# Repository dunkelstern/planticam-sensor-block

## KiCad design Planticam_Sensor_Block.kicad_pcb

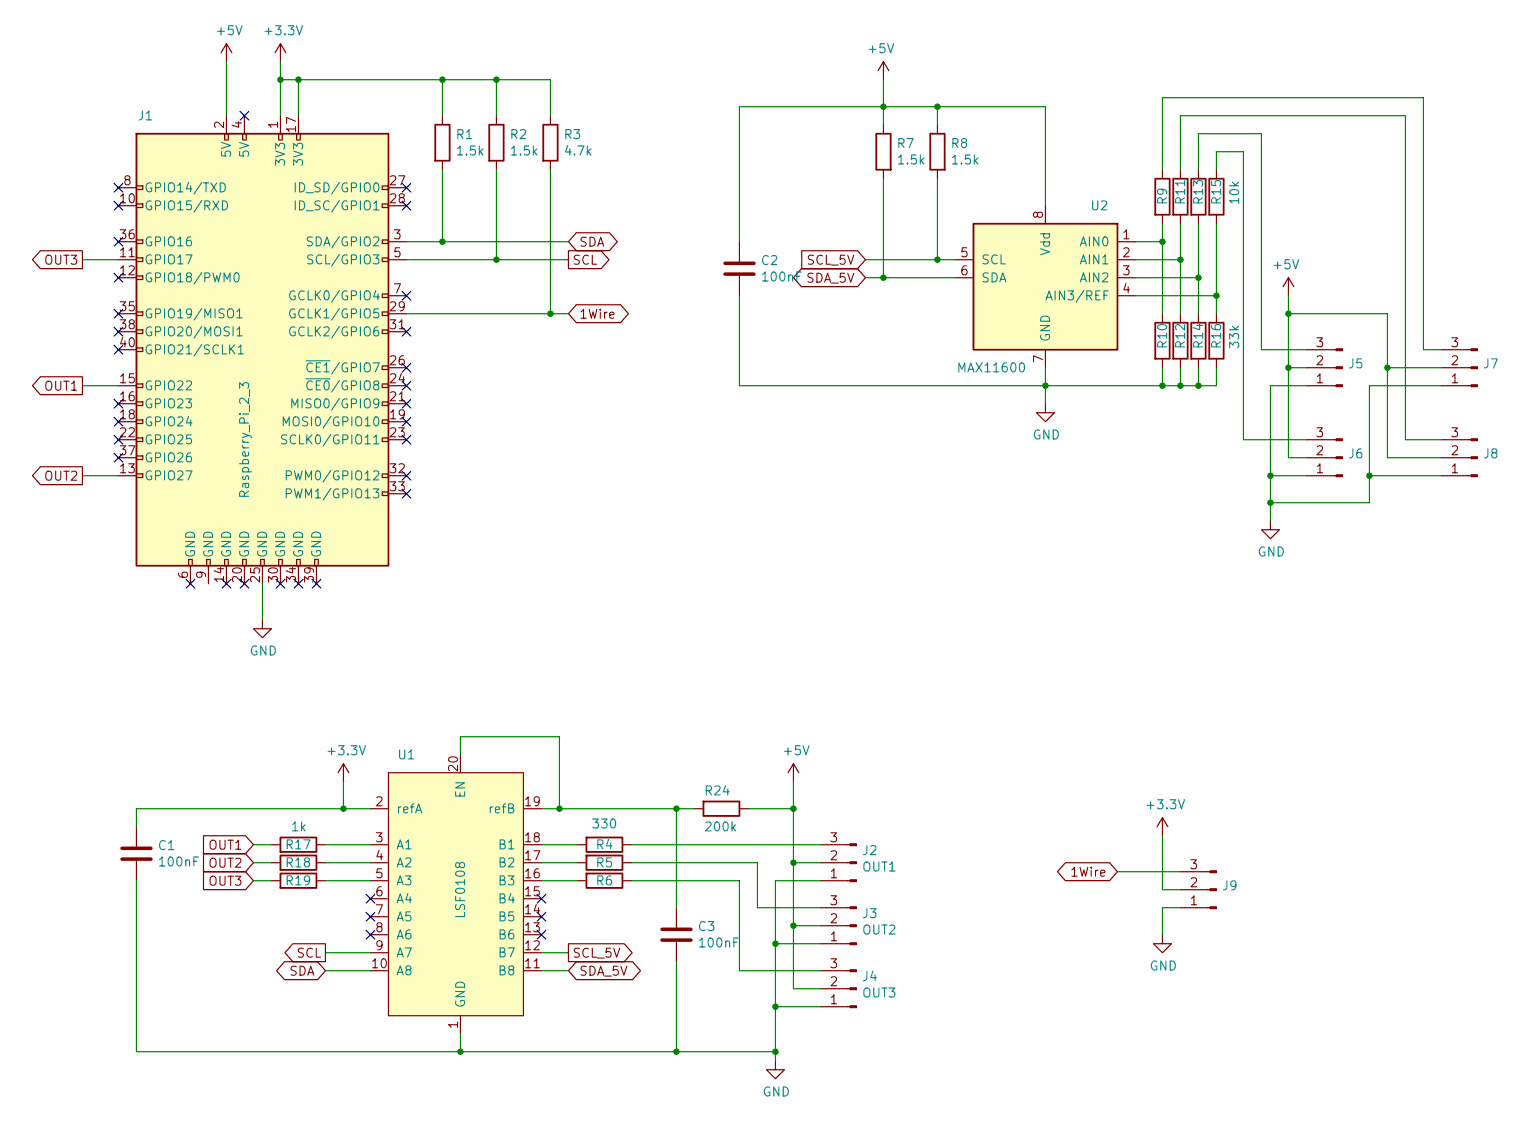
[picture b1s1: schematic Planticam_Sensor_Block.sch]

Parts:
C1, C2, C3: 100nF; R_0805_2012Metric_Pad1.20x1.40mm_HandSolder
J1: Raspberry_Pi_2_3; Raspberry_Pi_Zero_Socketed_THT_FaceDown_MountingHoles
J2: OUT1; JST_XH_B3B-XH-A_1x03_P2.50mm_Vertical
J3: OUT2; JST_XH_B3B-XH-A_1x03_P2.50mm_Vertical
J4: OUT3; JST_XH_B3B-XH-A_1x03_P2.50mm_Vertical
J5: AIN2; JST_PH_B3B-PH-K_1x03_P2.00mm_Vertical
J6: AIN3; JST_PH_B3B-PH-K_1x03_P2.00mm_Vertical
J7: AIN0; JST_PH_B3B-PH-K_1x03_P2.00mm_Vertical
J8: AIN1; JST_PH_B3B-PH-K_1x03_P2.00mm_Vertical
J9: 1Wire; PinHeader_1x03_P2.54mm_Vertical
R1, R2, R7, R8: 1.5k; R_0805_2012Metric_Pad1.20x1.40mm_HandSolder
R3: 4.7k; R_0805_2012Metric_Pad1.20x1.40mm_HandSolder
R4, R5, R6: 330; R_1206_3216Metric_Pad1.30x1.75mm_HandSolder
R9, R11, R13, R15: 10k; R_1206_3216Metric_Pad1.30x1.75mm_HandSolder
R10, R12, R14, R16: 33k; R_1206_3216Metric_Pad1.30x1.75mm_HandSolder
R17, R18, R19: 1k; R_0805_2012Metric_Pad1.20x1.40mm_HandSolder
R24: 200k; R_1206_3216Metric_Pad1.30x1.75mm_HandSolder
U1: LSF0108; TSSOP-20_4.4x6.5mm_P0.65mm
U2: MAX11600; SOT-23-8

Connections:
1Wire: J1.29 (GCLK1/GPIO5), J9.3, R3.2
+3V3: C1.1, J1.1 (3V3), J1.17 (3V3), J9.2, R1.1, R2.1, R3.1, U1.2 (refA)
+5V: C2.1, J1.2 (5V), J2.2, J3.2, J4.2, J5.2, J6.2, J7.2, J8.2, R7.1, R8.1, R24.1, U2.8 (Vdd)
GND: C1.2, C2.2, C3.2, J1.25 (GND), J2.1, J3.1, J4.1, J5.1, J6.1, J7.1, J8.1, J9.1, R10.2, R12.2, R14.2, R16.2, U1.1 (GND), U2.7 (GND)
unnamed: C3.1, R24.2, U1.19 (refB), U1.20 (EN)
unnamed: J2.3, R4.1
unnamed: J3.3, R5.1
unnamed: J4.3, R6.1
unnamed: J5.3, R13.1
unnamed: J6.3, R15.1
unnamed: J7.3, R9.1
unnamed: J8.3, R11.1
unnamed: R4.2, U1.18 (B1)
unnamed: R5.2, U1.17 (B2)
unnamed: R6.2, U1.16 (B3)
unnamed: R9.2, R10.1, U2.1 (AIN0)
unnamed: R11.2, R12.1, U2.2 (AIN1)
unnamed: R13.2, R14.1, U2.3 (AIN2)
unnamed: R15.2, R16.1, U2.4 (AIN3/REF)
unnamed: R17.1, U1.3 (A1)
unnamed: R18.1, U1.4 (A2)
unnamed: R19.1, U1.5 (A3)
OUT1: J1.15 (GPIO22), R17.2
OUT2: J1.13 (GPIO27), R18.2
OUT3: J1.11 (GPIO17), R19.2
SCL: J1.5 (SCL/GPIO3), R2.2, U1.9 (A7)
SCL_5V: R8.2, U1.12 (B7), U2.5 (SCL)
SDA: J1.3 (SDA/GPIO2), R1.2, U1.10 (A8)
SDA_5V: R7.2, U1.11 (B8), U2.6 (SDA)

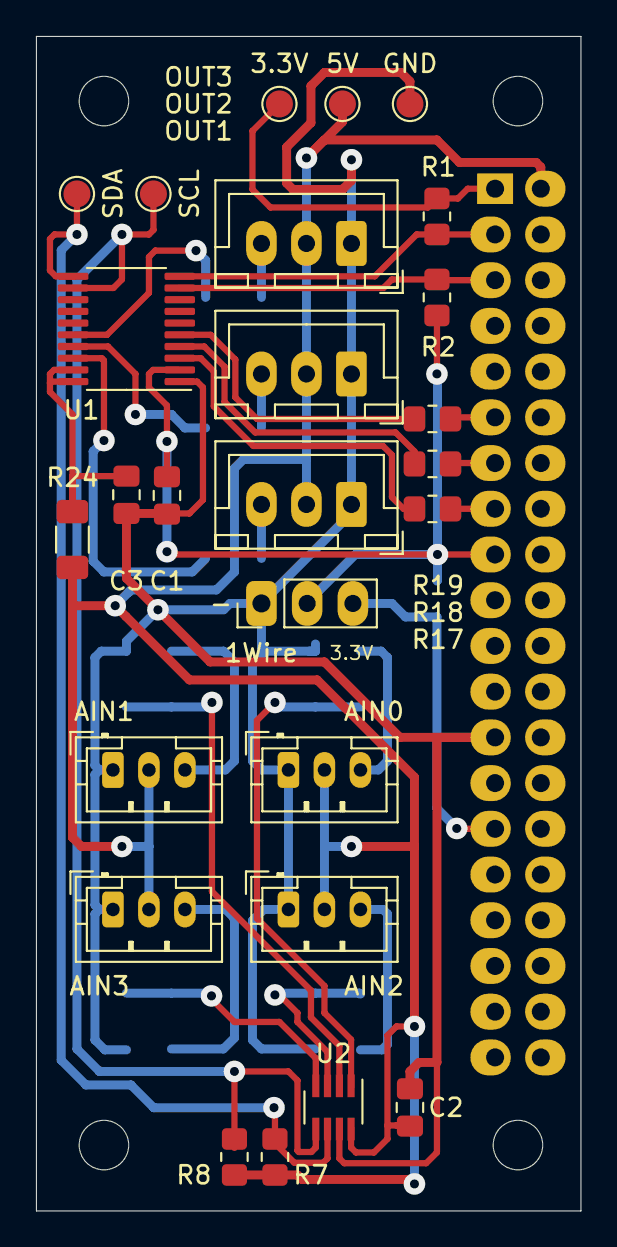
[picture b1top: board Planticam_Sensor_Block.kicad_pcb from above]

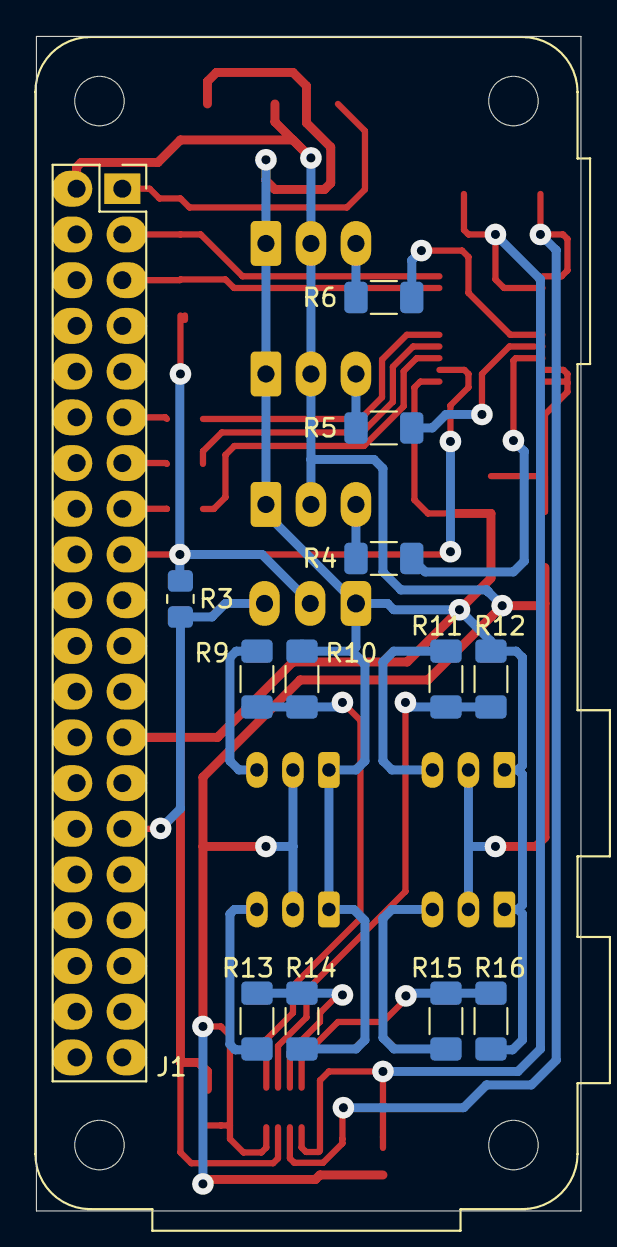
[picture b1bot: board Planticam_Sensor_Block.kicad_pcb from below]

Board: 2 copper layers, 30.2 x 65.2 mm, 39 parts (13 on the bottom side), 29 nets.

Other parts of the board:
3.3V, 5V: TestPoint_Pad_D1.5mm
GND: TestPoint_Pad_D1.5mm
SCL: TestPoint_Pad_D1.5mm
SDA: TestPoint_Pad_D1.5mm
